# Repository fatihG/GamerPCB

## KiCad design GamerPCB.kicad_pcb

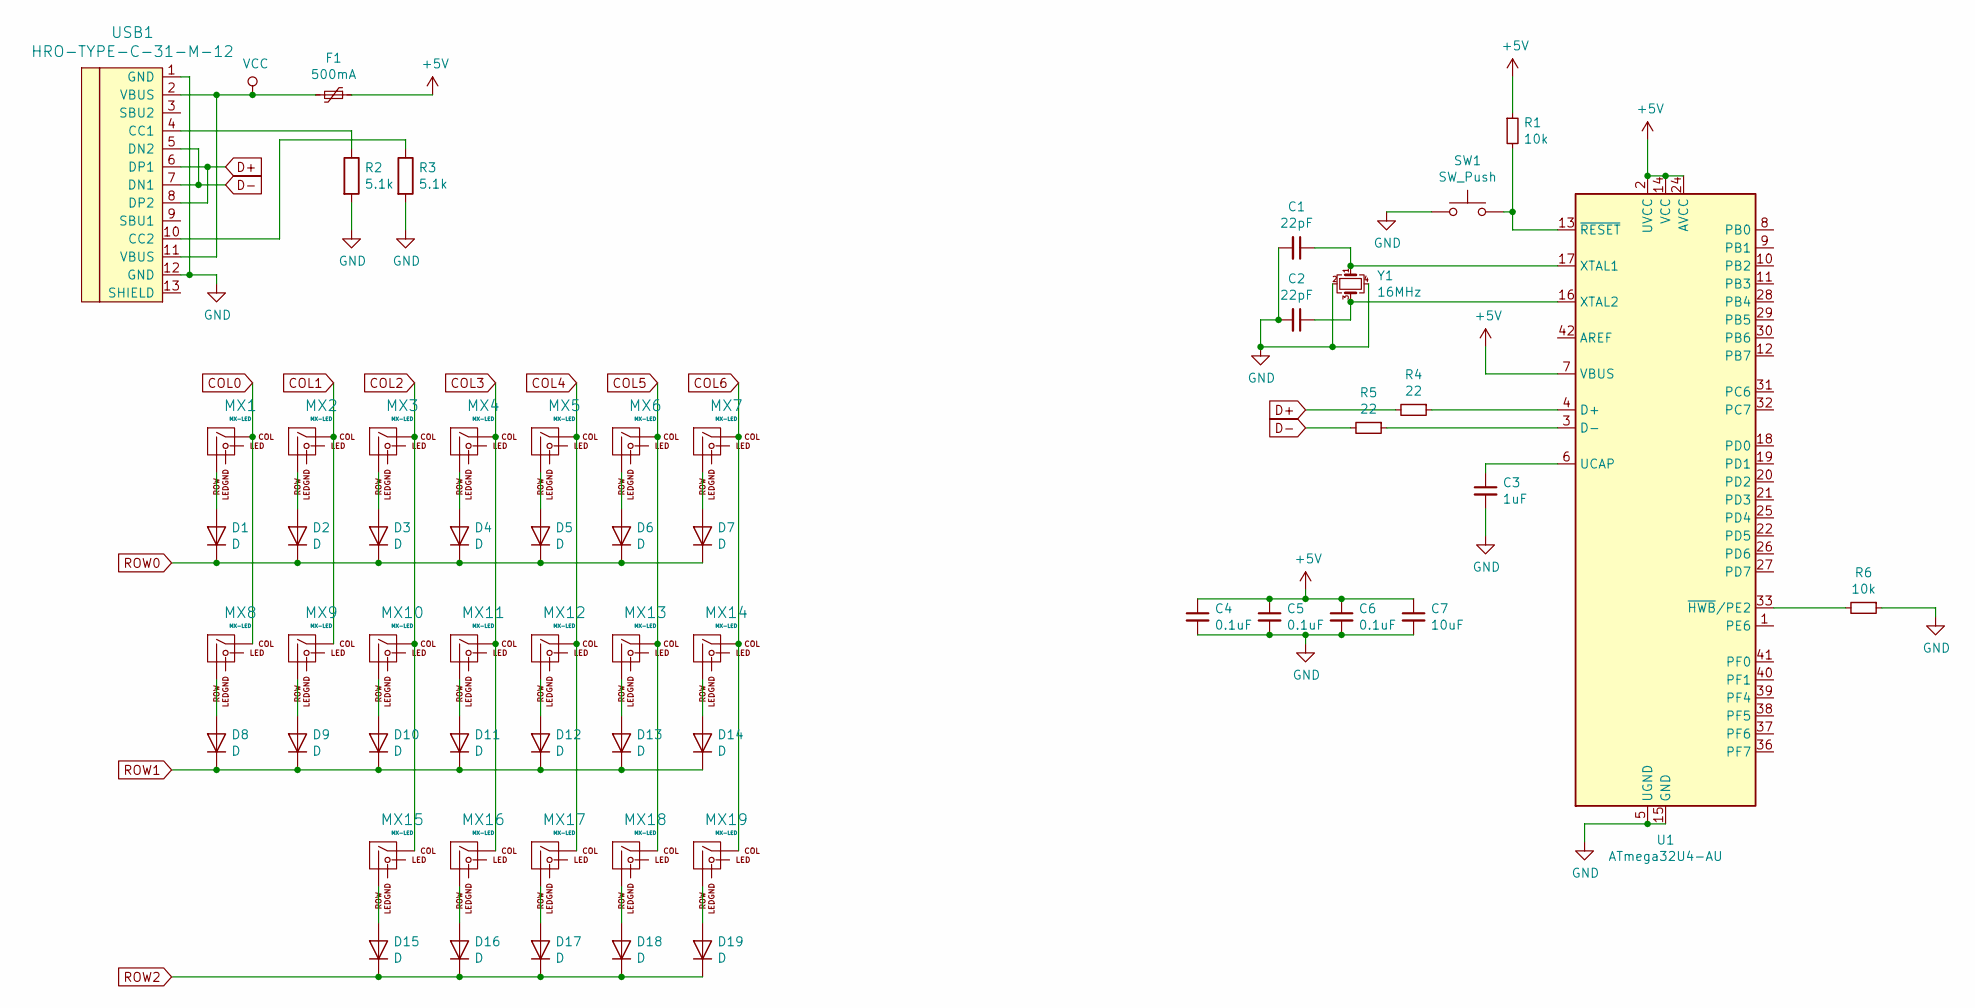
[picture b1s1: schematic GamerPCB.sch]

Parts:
C1, C2: 22pF; C_0805_2012Metric
C3: 1uF; C_0805_2012Metric
C4, C5, C6: 0.1uF; C_0805_2012Metric
C7: 10uF; D_SOD-123
D1, D2, D3, D4, D5, D6, D7, D8, D9, D10, D11, D12, D13, D14, D15, D16, D17, D18, D19: D; D_SOD-123
F1: 500mA; Fuse_1206_3216Metric
MX1, MX2, MX3, MX4, MX5, MX6, MX7, MX8, MX9, MX10, MX11, MX12, MX13, MX14, MX15, MX16, MX17, MX18, MX19: MX-LED; KailhChoc-1U
R1, R6: 10k; R_0805_2012Metric
R2, R3: 5.1k; R_0805_2012Metric
R4, R5: 22; R_0805_2012Metric
SW1: SW_Push; SKQG-1155865
U1: ATmega32U4-AU; TQFP-44_10x10mm_P0.8mm
USB1: HRO-TYPE-C-31-M-12; HRO-TYPE-C-31-M-12-Assembly
Y1: 16MHz; Crystal_SMD_3225-4Pin_3.2x2.5mm

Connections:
+5V: C4.1, C5.1, C6.1, C7.1, F1.1, R1.1, U1.2 (UVCC), U1.7 (VBUS), U1.14 (VCC), U1.24 (AVCC), U1.34 (VCC), U1.44 (AVCC)
COL0: MX1.1 (COL), MX8.1 (COL)
COL1: MX2.1 (COL), MX9.1 (COL)
COL2: MX3.1 (COL), MX10.1 (COL), MX15.1 (COL)
COL3: MX4.1 (COL), MX11.1 (COL), MX16.1 (COL)
COL4: MX5.1 (COL), MX12.1 (COL), MX17.1 (COL)
COL5: MX6.1 (COL), MX13.1 (COL), MX18.1 (COL)
COL6: MX7.1 (COL), MX14.1 (COL), MX19.1 (COL)
D+: R4.2, USB1.6 (DP1), USB1.8 (DP2)
D-: R5.2, USB1.5 (DN2), USB1.7 (DN1)
GND: C1.2, C2.2, C3.2, C4.2, C5.2, C6.2, C7.2, R2.2, R3.2, R6.1, SW1.1, U1.5 (UGND), U1.15 (GND), U1.23 (GND), U1.35 (GND), U1.43 (GND), USB1.1 (GND), USB1.12 (GND), Y1.2, Y1.4
unnamed: C1.1, U1.17 (XTAL1), Y1.1
unnamed: C2.1, U1.16 (XTAL2), Y1.3
unnamed: C3.1, U1.6 (UCAP)
unnamed: D1.2 (A), MX1.2 (ROW)
unnamed: D2.2 (A), MX2.2 (ROW)
unnamed: D3.2 (A), MX3.2 (ROW)
unnamed: D4.2 (A), MX4.2 (ROW)
unnamed: D5.2 (A), MX5.2 (ROW)
unnamed: D6.2 (A), MX6.2 (ROW)
unnamed: D7.2 (A), MX7.2 (ROW)
unnamed: D8.2 (A), MX8.2 (ROW)
unnamed: D9.2 (A), MX9.2 (ROW)
unnamed: D10.2 (A), MX10.2 (ROW)
unnamed: D11.2 (A), MX11.2 (ROW)
unnamed: D12.2 (A), MX12.2 (ROW)
unnamed: D13.2 (A), MX13.2 (ROW)
unnamed: D14.2 (A), MX14.2 (ROW)
unnamed: D15.2 (A), MX15.2 (ROW)
unnamed: D16.2 (A), MX16.2 (ROW)
unnamed: D17.2 (A), MX17.2 (ROW)
unnamed: D18.2 (A), MX18.2 (ROW)
unnamed: D19.2 (A), MX19.2 (ROW)
unnamed: R1.2, SW1.2, U1.13 (~RESET)
unnamed: R2.1, USB1.4 (CC1)
unnamed: R3.1, USB1.10 (CC2)
unnamed: R4.1, U1.4 (D+)
unnamed: R5.1, U1.3 (D-)
unnamed: R6.2, U1.33 (~HWB~/PE2)
ROW0: D1.1 (K), D2.1 (K), D3.1 (K), D4.1 (K), D5.1 (K), D6.1 (K), D7.1 (K)
ROW1: D8.1 (K), D9.1 (K), D10.1 (K), D11.1 (K), D12.1 (K), D13.1 (K), D14.1 (K)
ROW2: D15.1 (K), D16.1 (K), D17.1 (K), D18.1 (K), D19.1 (K)
VCC: F1.2, USB1.2 (VBUS), USB1.11 (VBUS)

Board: 2 copper layers, 56 parts (0 on the bottom side), 43 nets, no tracks yet.

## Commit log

2022-02-13 Add submodules
2022-02-13 KiCad setup
    Setting up libraries from submodules in KiCad
2022-02-13 Schemetic
2022-02-13 USB C connector
2022-02-14 Initial PCB Design
2022-02-18 add marbastlib
2022-02-18 KiCad Update
